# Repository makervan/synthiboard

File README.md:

# Synthiboard

An Arduino-based synthesizer, with multiple firmwares to allow for different sounds. See http://wiki.makervan.de/wiki/Synthiboard for more information.

## Firmware
There are multiple firmwares available for the Synthiboard, you can find some in this repository.
* Auduino
* R2R Drum Machine
* Glitch Storm by [Spherical Sound Society](https://github.com/spherical-sound-society/glitch-storm), adapted to work with Synthiboard pinout.

## License
Hardware designs created by Severin Schols, and shared under CC-BY-SA-4.0. See LICENSE for more information.

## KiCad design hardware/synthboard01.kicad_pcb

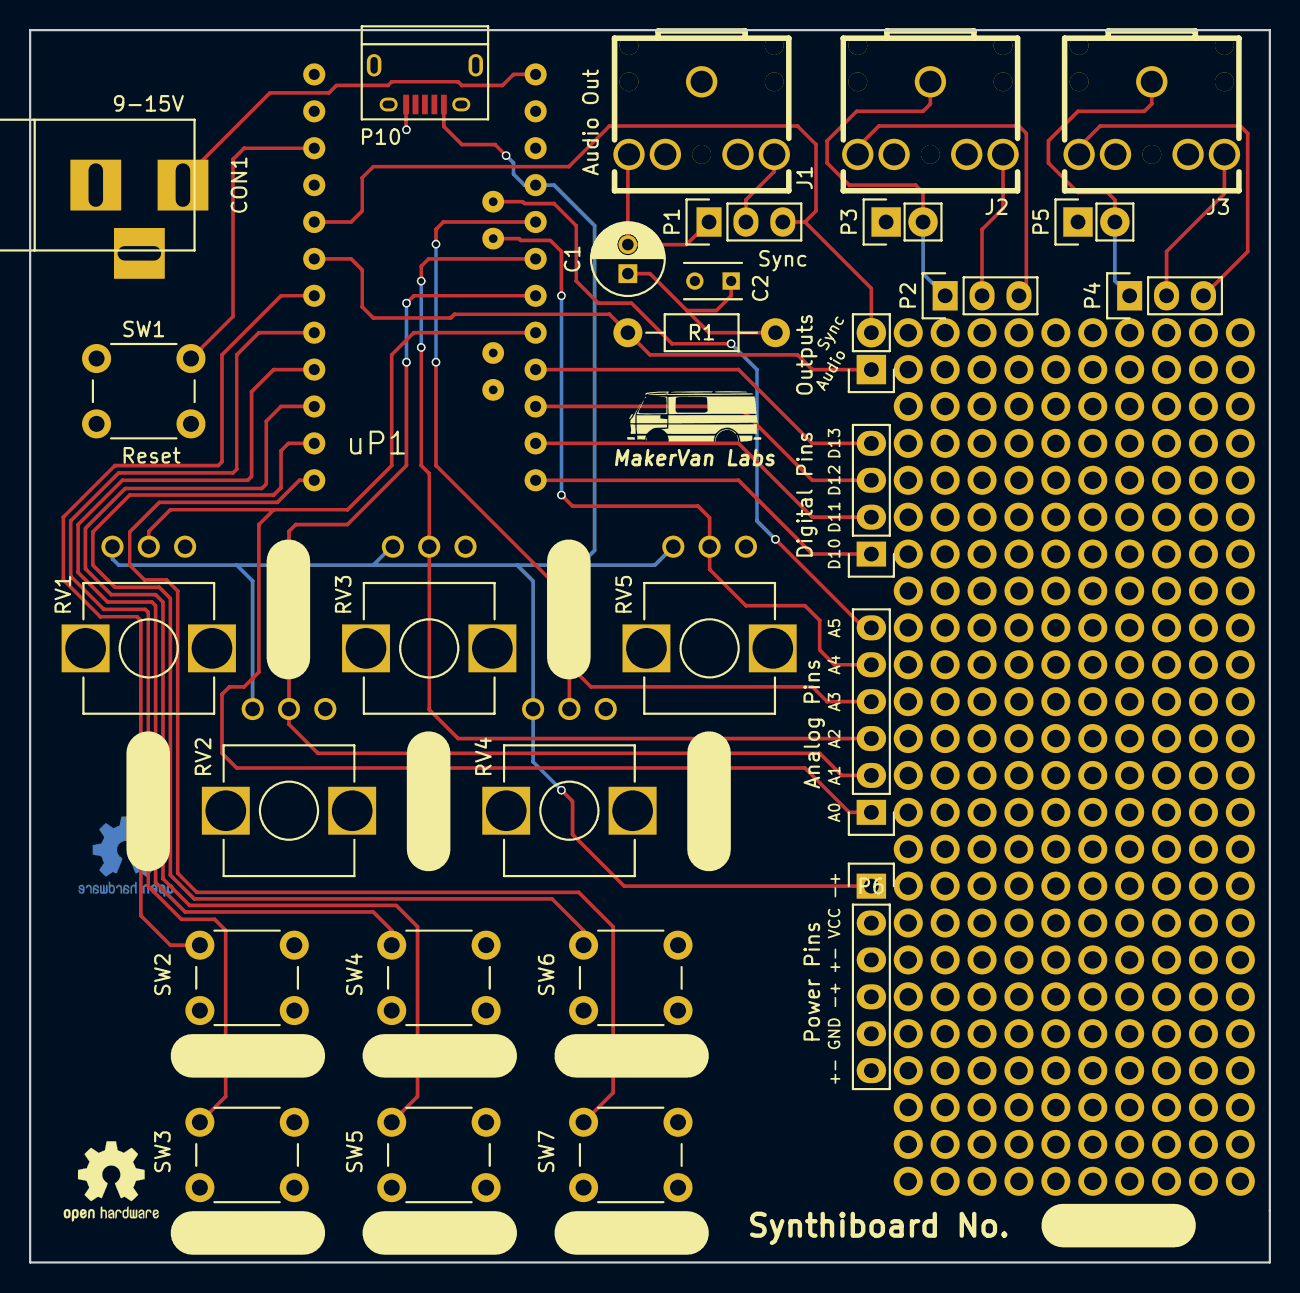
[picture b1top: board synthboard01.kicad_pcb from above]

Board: 2 copper layers, 85.3 x 84.8 mm, 30 parts (0 on the bottom side), 31 nets.

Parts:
C1: 10µ; C_Radial_D5_L11_P2
C2: 10n; C_Rect_L4_W2.5_P2.5
CON1: 9-15V; BARREL_JACK
J1: Audio Out; AudioJack3.5mm
J2: Addit. Plug 1; AudioJack3.5mm
J3: Addit. Plug 2; AudioJack3.5mm
P1: Sync; Pin_Header_Straight_1x03
P2: AP1; Pin_Header_Straight_1x03
P3: AP1_GND; Pin_Header_Straight_1x02
P4: AP2; Pin_Header_Straight_1x03
P5: AP2_GND; Pin_Header_Straight_1x02
P6: Analog Pins; Pin_Header_Straight_1x06
P7: Digital Pins; Pin_Header_Straight_1x04
P8: Power Pins; Pin_Header_Straight_1x06
P9: Outputs; Pin_Header_Straight_1x02
P10: USB_OTG; USB_Micro-B
R1: 1k; Resistor_Horizontal_RM10mm
RV1, RV2, RV3, RV4, RV5: 10k; Potentiometer_Alpha-RV09
SW1: Reset; SW_PUSH_6mm
SW2: Button 1; SW_PUSH_6mm
SW3: Button 2; SW_PUSH_6mm
SW4: Button 3; SW_PUSH_6mm
SW5: Button 4; SW_PUSH_6mm
SW6: Button 5; SW_PUSH_6mm
SW7: Button 6; SW_PUSH_6mm
uP1: ARDUPROMINI-6; ArduProMini-6

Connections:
+9V: CON1.1, uP1.19
A0: P6.1, RV1.2, uP1.26
A1: P6.2, RV2.2, uP1.25
A2: P6.3, RV3.2, uP1.24
A3: P6.4, RV4.2, uP1.23
A4: P6.5, RV5.2, uP1.32
A5: P6.6, uP1.31
AudioOut: P9.1, R1.2, uP1.12
D10: P7.1, uP1.30
D11: P7.2, uP1.29
D12: P7.3, uP1.28
D13: P7.4, uP1.27
GND: C2.2, CON1.2, J1.1, P3.1, P5.1, P8.4, P8.5, P8.6, P10.5, RV1.1, RV2.1, RV3.1, RV4.1, RV5.1, SW1.2, SW2.2, SW3.2, SW4.2, SW5.2, SW6.2, SW7.2, uP1.10
unnamed: C1.1, C2.1, R1.1
unnamed: C1.2, J1.2, P1.1
unnamed: J1.3, P1.2
unnamed: J2.1, P2.1, P3.2
unnamed: J2.2, P2.3
unnamed: J2.3, P2.2
unnamed: J3.1, P4.1, P5.2
unnamed: J3.2, P4.3
unnamed: J3.3, P4.2
unnamed: SW1.1, uP1.9
unnamed: SW2.1, uP1.13
unnamed: SW3.1, uP1.14
unnamed: SW4.1, uP1.15
unnamed: SW5.1, uP1.16
unnamed: SW6.1, uP1.17
unnamed: SW7.1, uP1.18
Sync: P1.3, P9.2, uP1.11
VCC: P8.1, P8.2, P8.3, P10.1, RV1.3, RV2.3, RV3.3, RV4.3, RV5.3, uP1.22

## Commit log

2017-08-06 readme
2017-12-11 license
2017-12-28 sync input
2017-12-28 initial OLED display support
2021-12-11 Add glitch storm code
2021-12-11 Fix regular R2R Drum Machine
2022-02-22 add ellitone multi synth source
2026-03-22 v0.1 pictures
2026-03-22 migrate v0.1 to kicad 9

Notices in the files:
hardware/synthboard01.kicad_pcb:
Licensed under CC BY-SA 4.0
